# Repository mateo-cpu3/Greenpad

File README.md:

# Kyle's GREEN Macropad

---

It's special because it's green nothing else. this is my first macropad or engineering project in general so its not perfect, but I did spend a lot of time figuring everything out especially since I wanted it to be 3 x 3 not just 3 keys. 

---

# Challenges 

literally everything I had to restart because I didn't know you had to space the keys 19.05mm and ended messing everything up because I couldn't figure out why it didn't align with the case I also found the fusion interface super confusing, my mouse wheel broke halfway so zooming in and out was a pain

---

---

# BOM

* 9x Cherry MX switches
* 1x XIAO RP2040
* 4x M3 Heatset inserts
* M3 screws
* M3 Hex Nuts
* 9x 1N4148 diodes

---

# Schematic 

# PCB

# Case

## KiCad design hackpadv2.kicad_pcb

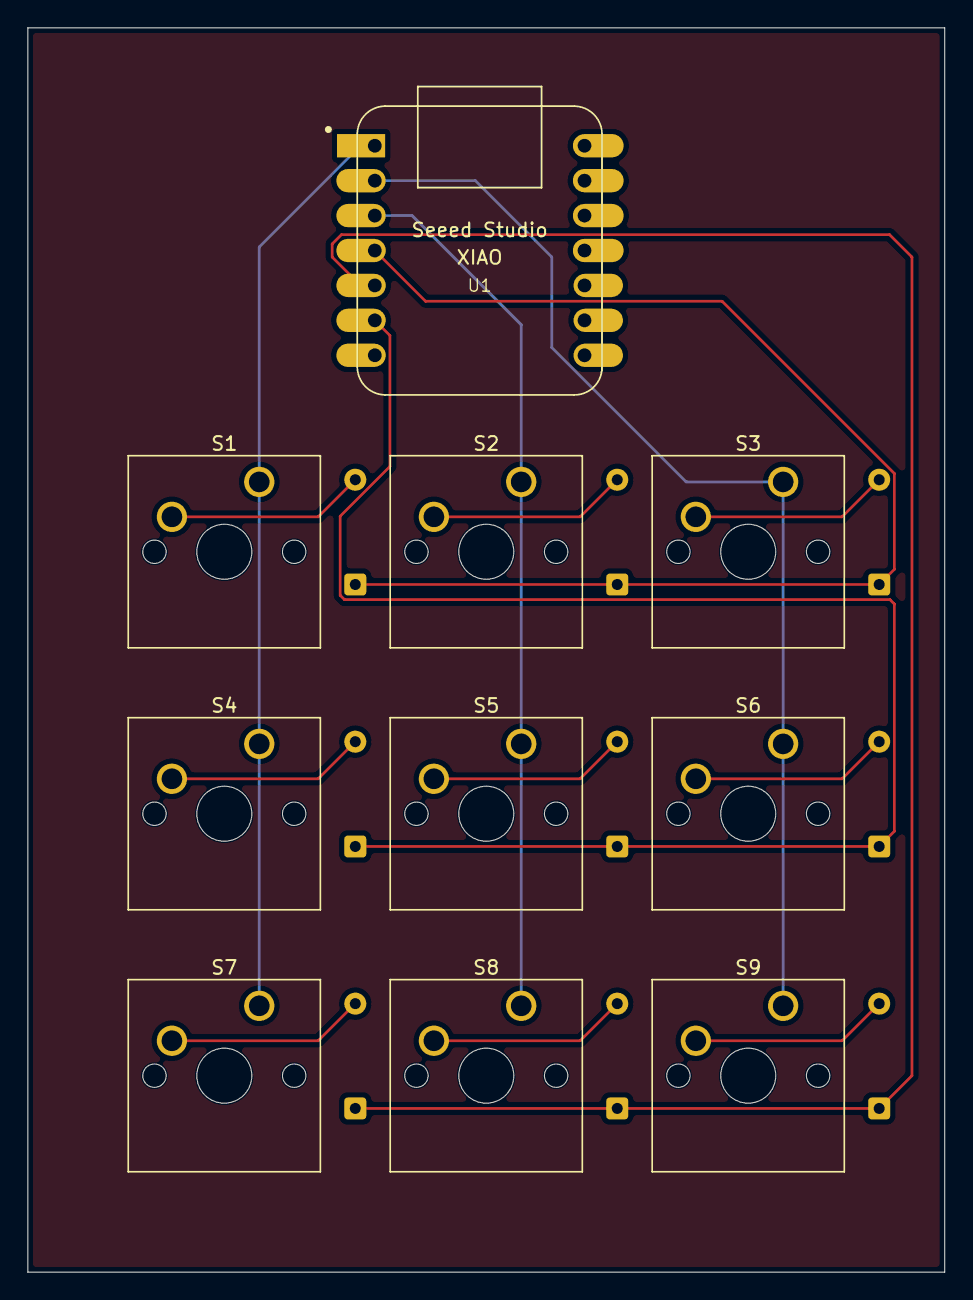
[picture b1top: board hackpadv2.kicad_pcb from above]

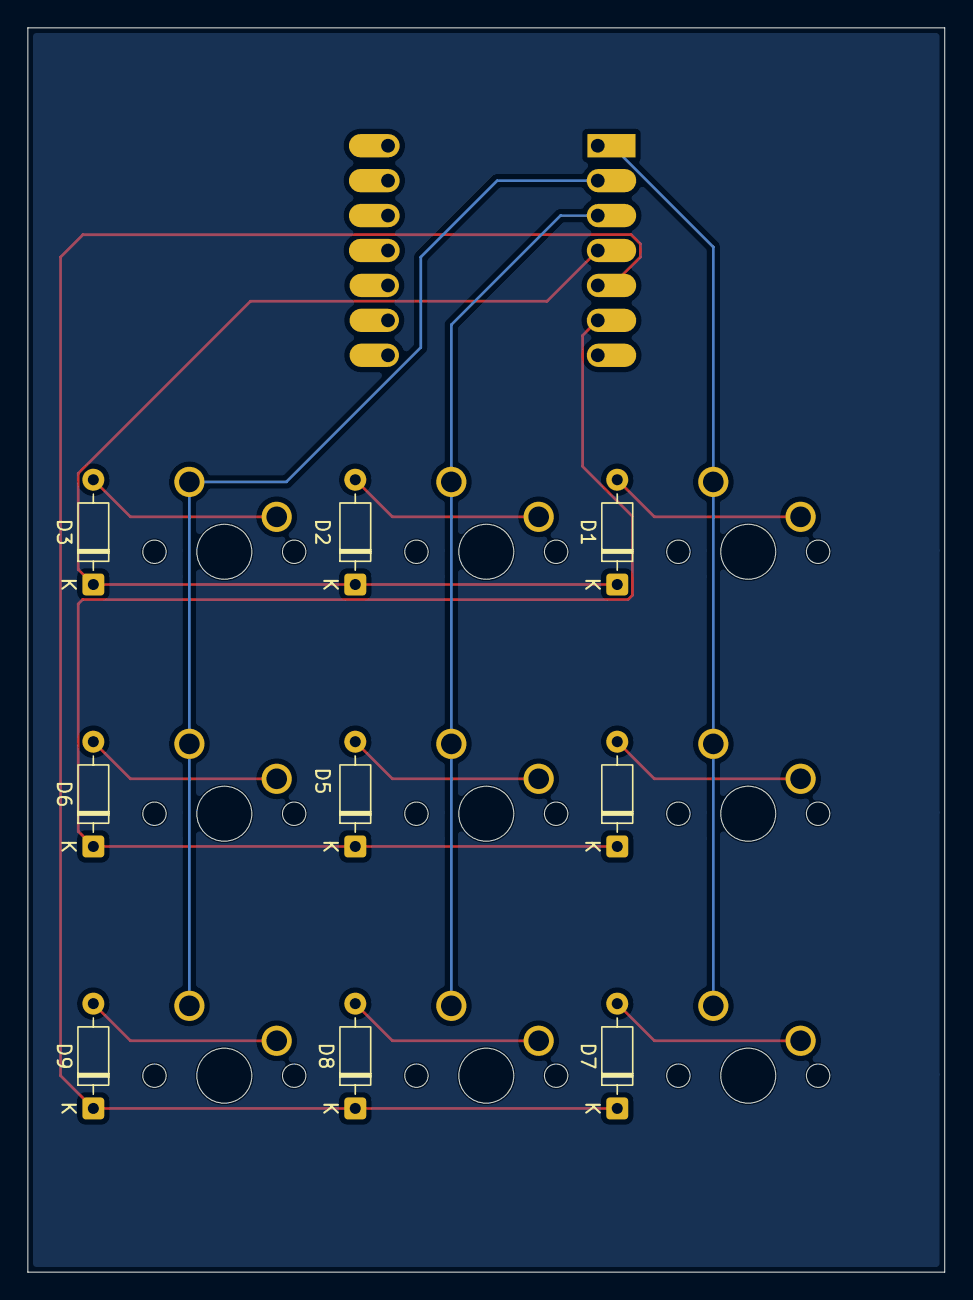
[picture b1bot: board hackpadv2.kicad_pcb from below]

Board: 2 copper layers, 66.7 x 90.5 mm, 19 parts (9 on the bottom side), 15 nets.

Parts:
D1, D2, D3, D4, D5, D6, D7, D8, D9: D_DO-35_SOD27_P7.62mm_Horizontal
S1, S2, S3, S4, S5, S6, S7, S8, S9: SW_Cherry_MX_1.00u_PCB
U1: MOUDLE-SEEEDUINO-XIAO; XIAO-Generic-Hybrid-14P-2.54-21X17.8MM

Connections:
Column 0: S1.1, S4.1, S7.1, U1.1 (PA02_A0_D0)
Column 1: S2.1, S5.1, S8.1, U1.3 (PA10_A2_D2)
Column 2: S3.1, S6.1, S9.1, U1.2 (PA4_A1_D1)
unnamed: D1.2 (A), S1.2
unnamed: D2.2 (A), S2.2
unnamed: D3.2 (A), S3.2
unnamed: D4.2 (A), S4.2
unnamed: D5.2 (A), S5.2
unnamed: D6.2 (A), S6.2
unnamed: D7.2 (A), S7.2
unnamed: D8.2 (A), S8.2
unnamed: D9.2 (A), S9.2
row 0: D1.1 (K), D2.1 (K), D3.1 (K), U1.4 (PA11_A3_D3)
row 1: D4.1 (K), D5.1 (K), D6.1 (K), U1.6 (PA9_A5_D5_SCL)
row 2: D7.1 (K), D8.1 (K), D9.1 (K), U1.5 (PA8_A4_D4_SDA)
